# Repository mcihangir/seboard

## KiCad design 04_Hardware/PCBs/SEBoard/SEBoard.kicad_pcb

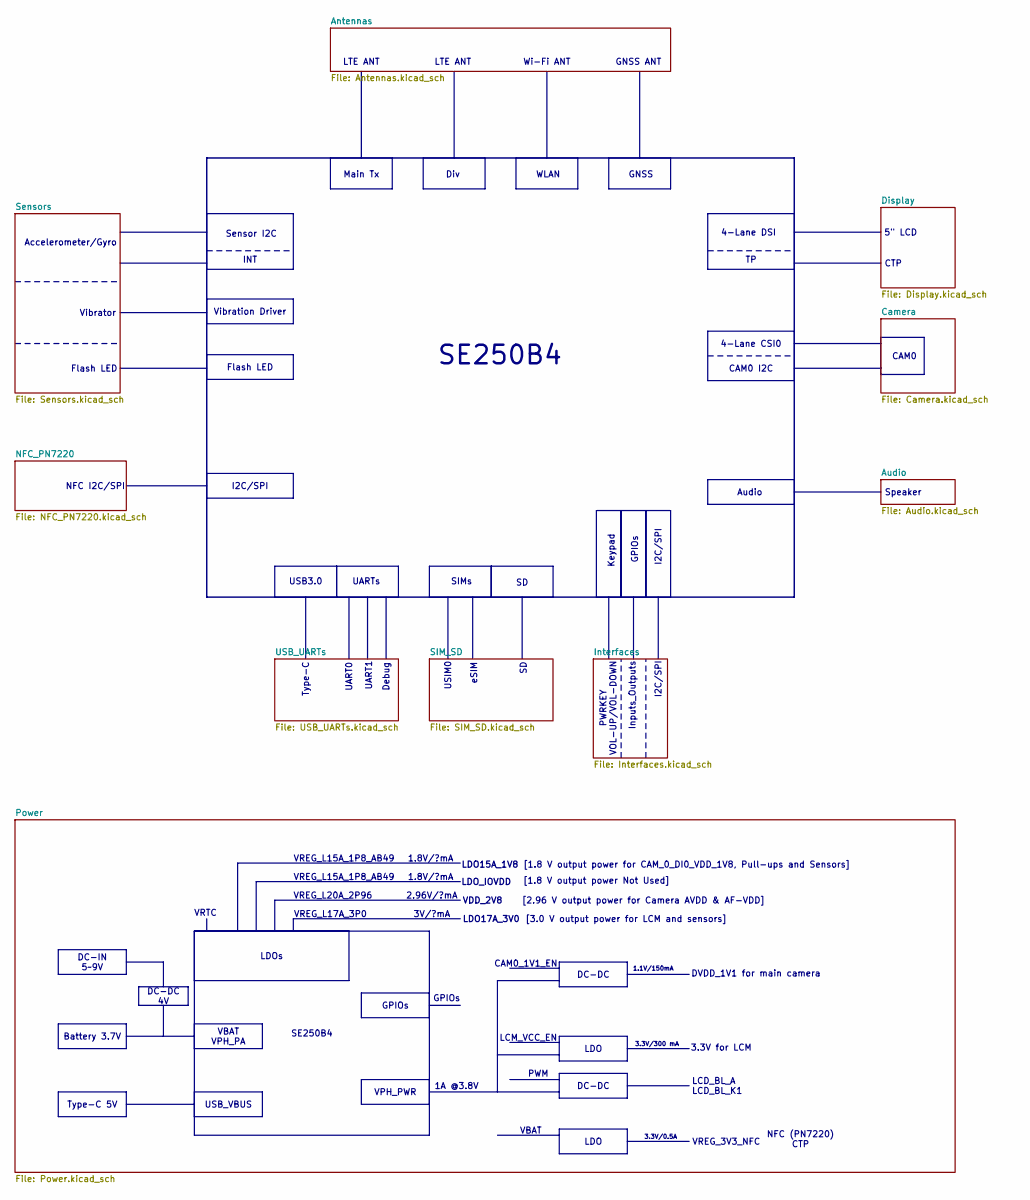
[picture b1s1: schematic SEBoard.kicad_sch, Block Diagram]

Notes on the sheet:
PWRKEY VOL-UP/VOL-DOWN
LDO17A_3V0
VREG_L15A_1P8_AB49
UARTs
Debug
GPIOs
I2C/SPI
Inputs_Outputs
USIM0
[1.8 V output power Not Used]
[3.0 V output power for LCM and sensors]
Flash LED
1.8V/?mA
4-Lane DSI
VRTC
1.1V/150mA
UART0
Accelerometer/Gyro
VREG_L20A_2P96
LCM_VCC_EN
USB3.0
SE250B4
VREG_L17A_3P0
1A @3.8V
Type-C
eSIM
2.96V/?mA
Vibration Driver
4-Lane CSI0
NFC I2C/SPI
Main Tx
Speaker
DVDD_1V1 for main camera
PWM
5" LCD
LCD_BL_A LCD_BL_K1
CAM0
GNSS
VDD_2V8
CAM0 I2C

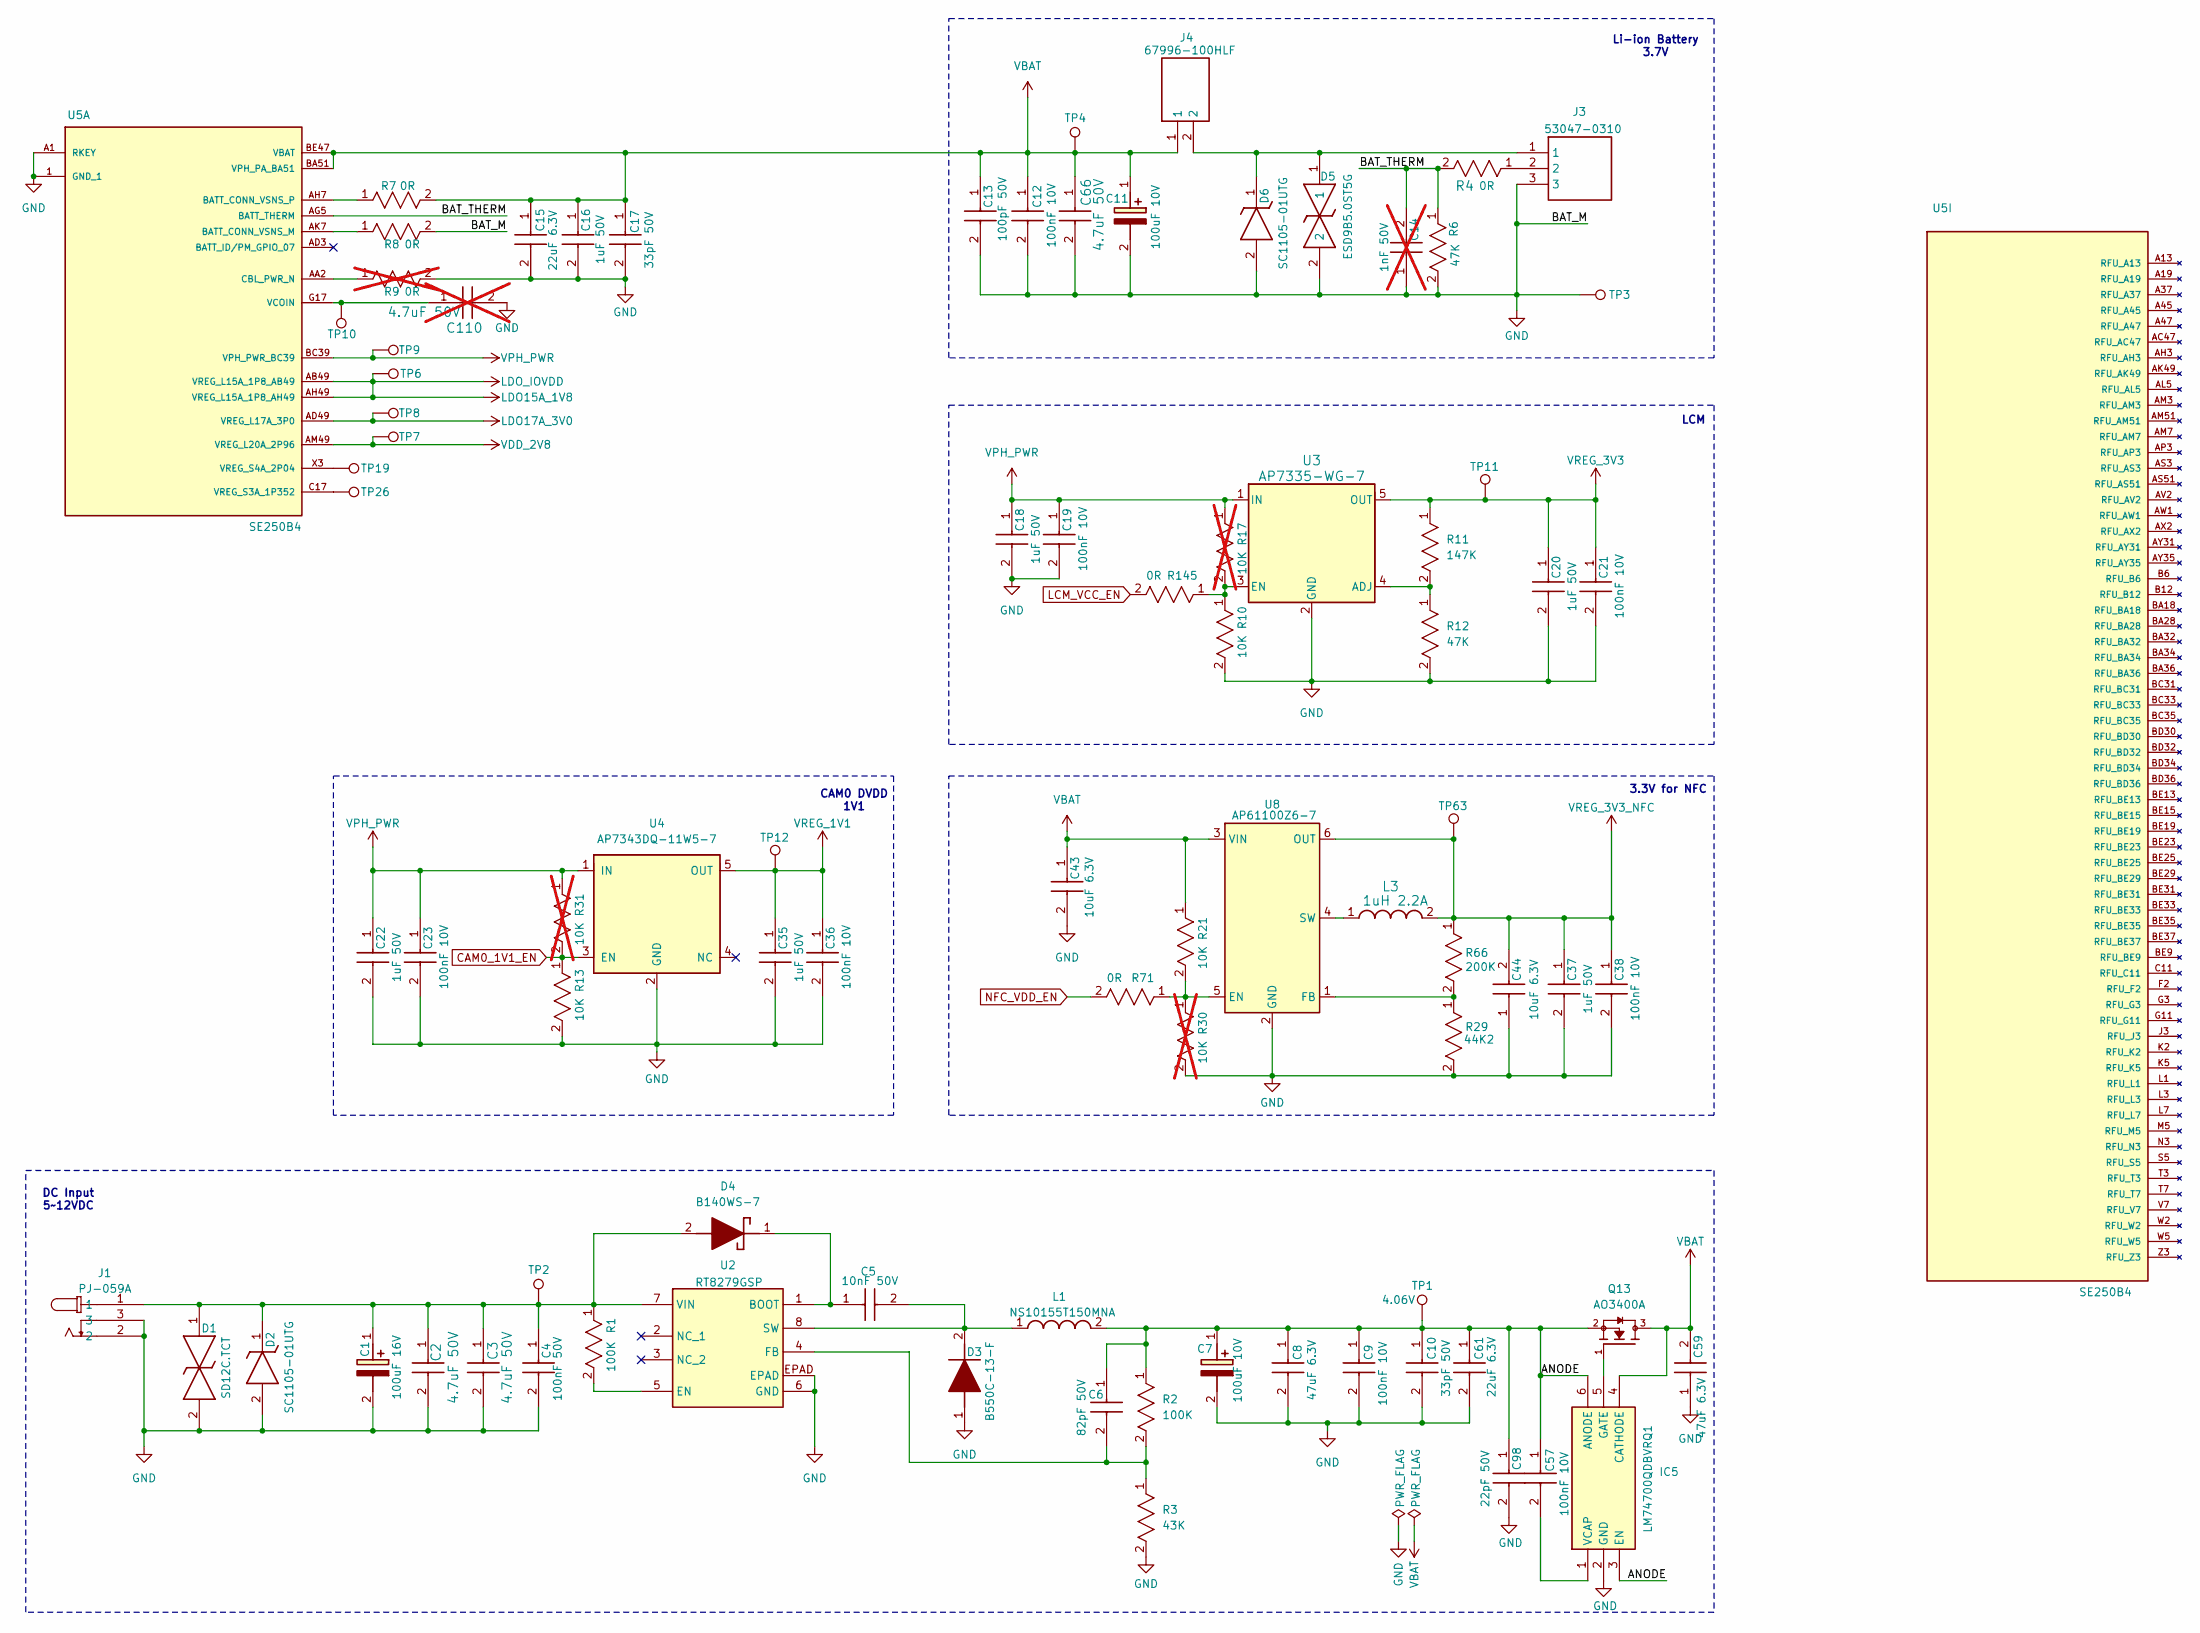
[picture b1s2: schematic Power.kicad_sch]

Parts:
C1: 100uF 16V; T495X; Part Number T495X107M016ATE1007280
C2, C3, C66: 4.7uF 50V; CAP_UMK325B7475MM-T_TAY; Part Number UMK325BJ475MM-T
C4: 100nF 50V; CAPC1005X55N; Part Number UMK105B7104KVHF
C5: 10nF 50V; CAPC1005X55N; Part Number GRM155R71H103KA88D
C6: 82pF 50V; CAPC1005X55N; Part Number GRM1555C1H820JA01D
C7, C11: 100uF 10V; T495D; Part Number T495D107K010ATE080
C8, C59: 47uF 6.3V; GRM31x; Part Number GRM31CR60J476ME19L
C9, C12, C19, C21, C23, C36, C38, C57: 100nF 10V; CAPC1005X55N; Part Number GRM155R71A104KA01D
C10, C17: 33pF 50V; CAPC1005X55N; Part Number GRM1555C1H330JA01D
C13: 100pF 50V; CAPC1005X55N; Part Number GRM1555C1H101JA01J
C14: 1nF 50V; CAPC1005X55N; Part Number GRM1555C1H102JA01D; not fitted
C15, C61: 22uF 6.3V; CAPC1005X55N; Part Number GRM158R60J226ME01D
C16, C18, C20, C22, C35, C37: 1uF 50V; CAPC1005X55N; Part Number GRM155R61H105KE05D
C43, C44: 10uF 6.3V; CAPC1005X55N; Part Number GRM155R60J106ME15D
C98: 22pF 50V; CAPC1005X55N; Part Number GRM1555C1H220JA01D
C110: 4.7uF 50V; CAP_UMK325B7475MM-T_TAY; Part Number UMK325BJ475MM-T; not fitted
D1: SD12C.TCT; SD12CTCT; Part Number SD12C.TCT
D2, D6: SC1105-01UTG; SC110501UTG; Part Number SC1105-01UTG
D3: B550C-13-F; DIOM7959X250N; Part Number B550C-13-F
D4: B140WS-7; SOD2513X120N; Part Number B140WS-7
D5: ESD9B5.0ST5G; SODFL1006X40N; Part Number ESD9B5.0ST5G
IC5: LM74700QDBVRQ1; SOT95P280X145-6N; Part Number LM74700QDBVRQ1
J1: PJ-059A; PJ059A; Part Number PJ-059A
J3: 53047-0310; 530470310; Part Number 53047-0310
J4: 67996-100HLF; HDRV2W67P254_2X1_254X483X858P; Part Number 67996-100HLF
L1: NS10155T150MNA; NS10165T220MNA; Part Number NS10155T150MNA
L3: 1uH 2.2A; IND_WE-LQS_2512_WRE; Part Number 74404024010
Q13: AO3400A; SOT95P280X125-3N; Part Number AO3400A
R1, R2: 100K; RC0402N_YAG; Part Number RC0402JR-07100KL
R3: 43K; RC0402N_YAG; Part Number RC0402JR-0743KL
R4, R7, R8, R71, R145: 0R; RC0402N_YAG; Part Number RC0402JR-070RL
R6, R12: 47K; RC0402N_YAG; Part Number RC0402JR-0747KL
R9: 0R; RC0402N_YAG; Part Number RC0402JR-070RL; not fitted
R10, R13, R21: 10K; RC0402N_YAG; Part Number RC0402JR-0710KL
R11: 147K; RC0402N_YAG; Part Number RC0402FR-07147KL
R17, R30, R31: 10K; RC0402N_YAG; Part Number RC0402JR-0710KL; not fitted
R29: 44K2; RC0402N_YAG; Part Number RC0402FR-0744K2L
R66: 200K; RC0402N_YAG; Part Number RC0402FR-07200KL
TP1, TP2: 4.06V; TestPoint_Pad_D1.0mm
TP3, TP11, TP12, TP63: Sens_P; TestPoint_Pad_D1.0mm
TP4: VBAT; TestPoint_Pad_D1.0mm
TP6, TP19, TP26: LDO_IOVDD; TestPoint_Pad_D1.0mm
TP7: VDD_2V8; TestPoint_Pad_D1.0mm
TP8: LDO17A_3V0; TestPoint_Pad_D1.0mm
TP9: VPH_PWR; TestPoint_Pad_D1.0mm
TP10: VRTC; TestPoint_Pad_D1.0mm
U2: RT8279GSP; SOP8L_EP1_RIT; Part Number RT8279GSP
U3: AP7335-WG-7; SOT95P285X145-5N; Part Number AP7335-WG-7
U4: AP7343DQ-11W5-7; SOT95P285X145-5N; Part Number AP7343DQ-11W5-7
U5: SE250B4; XCVR_SE250B4-NA; Part Number SE250B4-EU
U8: AP61100Z6-7; SOT50P162X60-6N; Part Number AP61100Z6-7

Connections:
/Power/ANODE: C6.1, C7.1 (+), C8.1, C9.1, C10.1, C57.1, C61.1, C98.1, IC5.3 (EN), IC5.6 (ANODE), L1.2, Q13.2, R2.1, TP1.1 (1_1)
/Power/BAT_THERM: C14.2, R4.2, R6.1, U5.AG5 (BATT_THERM)
CAM0_1V1_EN: R13.1, R31.2, U4.3 (EN); also elsewhere on the board
GND: C1.2 (-), C2.2, C3.2, C4.2, C7.2 (-), C8.2, C9.2, C10.2, C11.2 (-), C12.2, C13.2, C14.1, C15.2, C16.2, C17.2, C18.2, C19.2, C20.2, C21.2, C22.2, C23.2, C35.2, C36.2, C37.2, C38.2, C43.2, C44.1, C59.1, C61.2, C66.2, C98.2, C110.2, D1.2, D2.2 (A), D3.1 (A), D5.2, D6.2 (A), IC5.2 (GND), J1.2, J1.3, J3.3, R3.2, R6.2, R8.2, R9.2, R10.2, R12.2, R13.2, R29.2, R30.2, TP3.1 (1_1), U2.6 (GND), U2.EPAD, U3.2 (GND), U4.2 (GND), U5.1 (GND_1), U5.2 (GND_2), U5.3 (GND_3), U5.4 (GND_4), U5.5 (GND_5), U5.6 (GND_6), U5.7 (GND_7), U5.8 (GND_8), U5.9 (GND_9), U5.10 (GND_10), U5.11 (GND_11), U5.12 (GND_12), U5.13 (GND_13), U5.14 (GND_14), U5.15 (GND_15), U5.16 (GND_16), U5.17 (GND_17), U5.18 (GND_18), U5.19 (GND_19), U5.20 (GND_20), U5.21 (GND_21), U5.22 (GND_22), U5.23 (GND_23), U5.24 (GND_24), U5.25 (GND_25), U5.26 (GND_26), U5.27 (GND_27), U5.28 (GND_28), U5.29 (GND_29), U5.30 (GND_30), U5.31 (GND_31), U5.32 (GND_32), U5.33 (GND_33), U5.34 (GND_34), U5.35 (GND_35), U5.36 (GND_36), U5.37 (GND_37), U5.38 (GND_38), U5.39 (GND_39), U5.40 (GND_40), U5.41 (GND_41), U5.42 (GND_42), U5.43 (GND_43), U5.44 (GND_44), U5.45 (GND_45), U5.46 (GND_46), U5.47 (GND_47), U5.48 (GND_48), U5.49 (GND_49), U5.50 (GND_50), U5.51 (GND_51), U5.52 (GND_52), U5.53 (GND_53), U5.54 (GND_54), U5.55 (GND_55), U5.56 (GND_56), U5.57 (GND_57), U5.58 (GND_58), U5.59 (GND_59), U5.60 (GND_60), U5.A1 (RKEY), U5.A7 (GND_A7), U5.A11 (GND_A11), U5.A15 (GND_A15), U5.A17 (GND_A17), U5.A21 (GND_A21), U5.A23 (GND_A23), U5.A27 (GND_A27), U5.A29 (GND_A29), U5.A31 (GND_A31), U5.A35 (GND_A35), U5.A39 (GND_A39), U5.A43 (GND_A43), U5.AA5 (GND_AA5), U5.AA47 (GND_AA47), U5.AB45 (GND_AB45), U5.AB51 (GND_AB51), U5.AC50 (GND_AC50), U5.AD7 (GND_AD7), U5.AE5 (GND_AE5), U5.AF3 (GND_AF3), U5.AF45 (GND_AF45), U5.AG2 (GND_AG2), U5.AH1 (GND_AH1), U5.AH51 (GND_AH51), U5.AJ2 (GND_AJ2), U5.AJ5 (GND_AJ5), U5.AJ47 (GND_AJ47), U5.AK3 (GND_AK3), U5.AK45 (GND_AK45), U5.AK51 (GND_AK51), U5.AL2 (GND_AL2), U5.AL47 (GND_AL47), U5.AM1 (GND_AM1), U5.AM45 (GND_AM45), U5.AN2 (GND_AN2), U5.AN50 (GND_AN50), U5.AP1 (GND_AP1), U5.AP51 (GND_AP51), U5.AR2 (GND_AR2), U5.AS1 (GND_AS1), U5.AT2 (GND_AT2), U5.AU1 (GND_AU1), U5.AU45 (GND_AU45), U5.AU51 (GND_AU51), U5.AV47 (GND_AV47), U5.AV50 (GND_AV50), U5.AW49 (GND_AW49), U5.AY1 (GND_AY1), U5.AY11 (GND_AY11), U5.AY17 (GND_AY17), U5.AY19 (GND_AY19), U5.AY29 (GND_AY29), U5.AY33 (GND_AY33), U5.AY37 (GND_AY37), U5.AY39 (GND_AY39), U5.AY41 (GND_AY41), U5.AZ2 (GND_AZ2), U5.B8 (GND_B8), U5.B10 (GND_B10), U5.B14 (GND_B14), U5.B16 (GND_B16), U5.B18 (GND_B18), U5.B24 (GND_B24), U5.B26 (GND_B26), U5.B28 (GND_B28), U5.B32 (GND_B32), U5.B34 (GND_B34), U5.B40 (GND_B40), U5.B42 (GND_B42), U5.BA1 (GND_BA1), U5.BA12 (GND_BA12), U5.BA20 (GND_BA20), U5.BA26 (GND_BA26), U5.BA30 (GND_BA30), U5.BA38 (GND_BA38), U5.BA40 (GND_BA40), U5.BA42 (GND_BA42), U5.BC13 (GND_BC13), U5.BC23 (GND_BC23), U5.BC29 (GND_BC29), U5.BC37 (GND_BC37), U5.BC45 (GND_BC45), U5.BD14 (GND_BD14), U5.BD24 (GND_BD24), U5.BD38 (GND_BD38), U5.BD44 (GND_BD44), U5.BE7 (GND_BE7), U5.BE11 (GND_BE11), U5.BE17 (GND_BE17), U5.BE21 (GND_BE21), U5.BE27 (GND_BE27), U5.BE39 (GND_BE39), U5.BE41 (GND_BE41), U5.C7 (GND_C7), U5.C9 (GND_C9), U5.C13 (GND_C13), U5.C15 (GND_C15), U5.C33 (GND_C33), U5.C41 (GND_C41), U5.E10 (GND_E10), U5.F50 (GND_F50), U5.G1 (GND_G1), U5.H2 (GND_H2), U5.J1 (GND_J1), U5.J51 (GND_J51), U5.M47 (GND_M47), U5.M50 (GND_M50), U5.N7 (GND_N7), U5.N49 (GND_N49), U5.N51 (GND_N51), U5.P47 (GND_P47), U5.P50 (GND_P50), U5.R3 (GND_R3), U5.T45 (GND_T45), U5.U5 (GND_U5), U5.V3 (GND_V3), U5.X1 (GND_X1), U5.Y2 (GND_Y2), U5.Y5 (GND_Y5), U8.2 (GND); also elsewhere on the board
LCM_VCC_EN: R145.2; also elsewhere on the board
LDO15A_1V8: TP6.1 (1_1), U5.AB49 (VREG_L15A_1P8_AB49), U5.AH49 (VREG_L15A_1P8_AH49); also elsewhere on the board
LDO17A_3V0: TP8.1 (1_1), U5.AD49 (VREG_L17A_3P0); also elsewhere on the board
NFC_VDD_EN: R71.2; also elsewhere on the board
unnamed: C1.1 (+), C2.1, C3.1, C4.1, D1.1, D2.1 (K), D4.2 (A), J1.1, R1.1, TP2.1 (1_1), U2.7 (VIN)
unnamed: C5.2, D3.2 (K), L1.1, U2.8 (SW)
unnamed: C5.1, D4.1 (K), U2.1 (BOOT)
unnamed: D5.1, D6.1 (K), J3.1, J4.2
unnamed: IC5.5 (GATE), Q13.1
unnamed: C57.2, IC5.1 (VCAP)
unnamed: J3.2, R4.1
unnamed: R1.2, U2.5 (EN)
unnamed: C6.2, R2.2, R3.1, U2.4 (FB)
unnamed: R11.2, R12.1, U3.4 (ADJ)
unnamed: R10.1, R17.2, R145.1, U3.3 (EN)
unnamed: R8.1, U5.AK7 (BATT_CONN_VSNS_M)
unnamed: R7.1, U5.AH7 (BATT_CONN_VSNS_P)
unnamed: R9.1, U5.AA2 (CBL_PWR_N)
unnamed: C110.1, TP10.1 (1_1), U5.G17 (VCOIN)
unnamed: TP26.1 (1_1), U5.C17 (VREG_S3A_1P352)
unnamed: TP19.1 (1_1), U5.X3 (VREG_S4A_2P04)
unnamed: R21.2, R30.1, R71.1, U8.5 (EN)
unnamed: R29.1, R66.2, U8.1 (FB)
unnamed: L3.1, U8.4 (SW)
VBAT: C11.1 (+), C12.1, C13.1, C15.1, C16.1, C17.1, C43.1, C59.2, C66.1, IC5.4 (CATHODE), J4.1, Q13.3, R7.2, R21.1, TP4.1 (1_1), U5.AW51 (VPH_PA_AW51), U5.AX50 (VPH_PA_AX50), U5.AY49 (VPH_PA_AY49), U5.AY51 (VPH_PA_AY51), U5.AZ50 (VPH_PA_AZ50), U5.BA51 (VPH_PA_BA51), U5.BC41 (VPH_PA_BC41), U5.BD42 (VPH_PA_BD42), U5.BE47 (VBAT), U8.3 (VIN); also elsewhere on the board
VDD_2V8: TP7.1 (1_1), U5.AM49 (VREG_L20A_2P96); also elsewhere on the board
VPH_PWR: C18.1, C19.1, C22.1, C23.1, R17.1, R31.1, TP9.1 (1_1), U3.1 (IN), U4.1 (IN), U5.BC39 (VPH_PWR_BC39), U5.BC43 (VPH_PWR_BC43), U5.BD40 (VPH_PWR_BD40), U5.BD46 (VPH_PWR_BD46), U5.BE43 (VPH_PWR_BE43), U5.BE45 (VPH_PWR_BE45); also elsewhere on the board
VREG_1V1: C35.1, C36.1, TP12.1 (1_1), U4.5 (OUT); also elsewhere on the board
VREG_3V3: C20.1, C21.1, R11.1, TP11.1 (1_1), U3.5 (OUT); also elsewhere on the board
VREG_3V3_NFC: C37.1, C38.1, C44.2, L3.2, R66.1, TP63.1 (1_1), U8.6 (OUT); also elsewhere on the board

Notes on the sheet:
3.3V for NFC
Li-ion Battery 3.7V
CAM0 DVDD 1V1
LCM
DC Input 5~12VDC

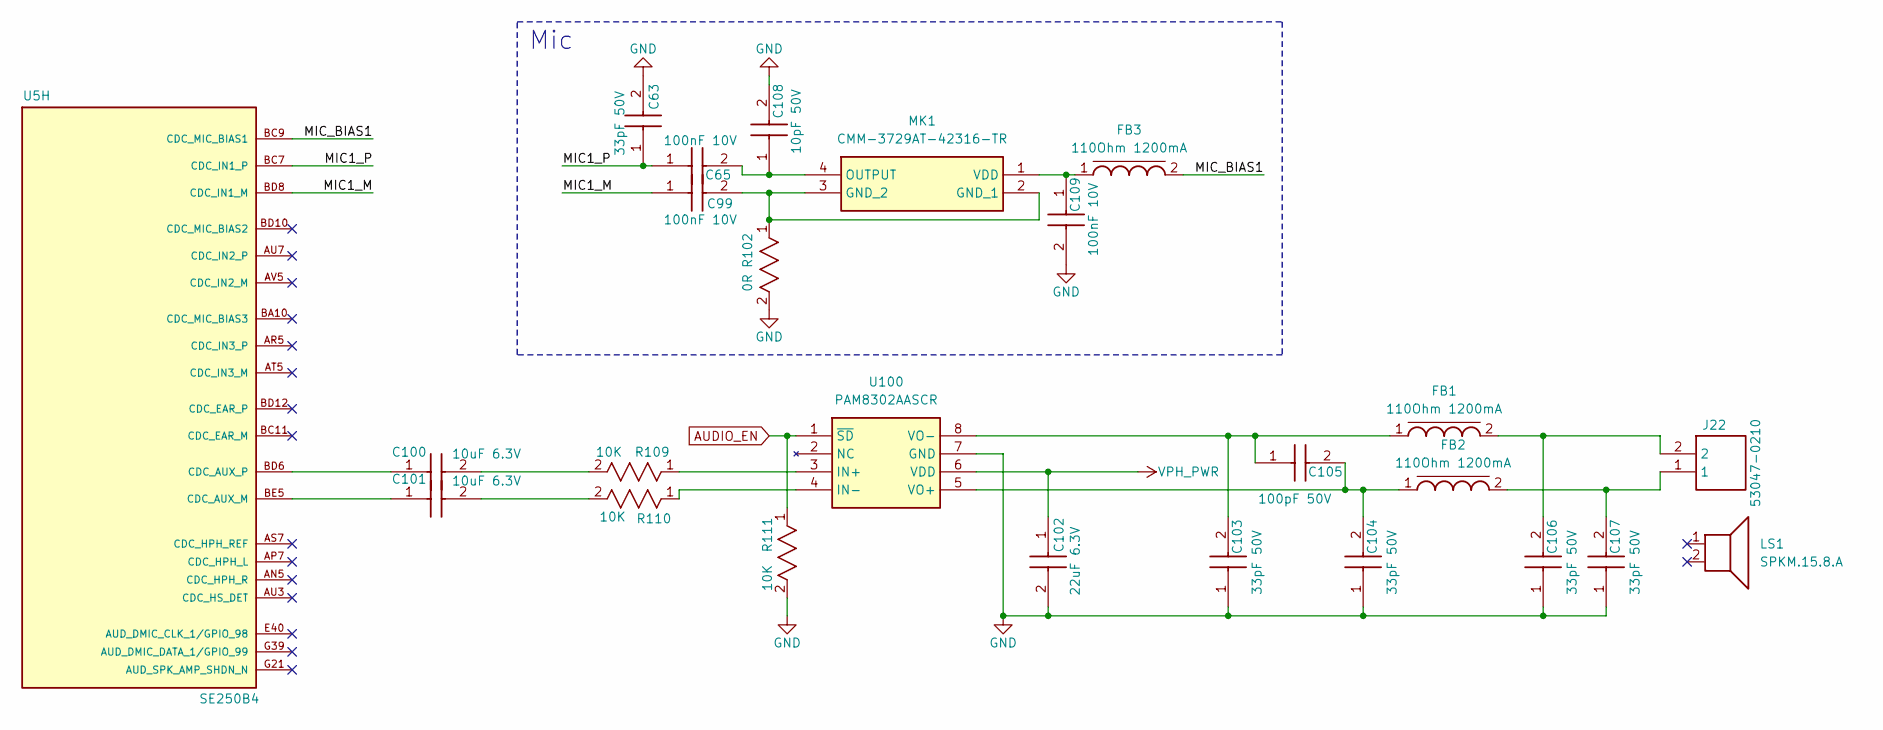
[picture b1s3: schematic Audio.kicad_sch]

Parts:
C63, C103, C104, C106, C107: 33pF 50V; CAPC1005X55N; Part Number GRM1555C1H330JA01D
C65, C99, C109: 100nF 10V; CAPC1005X55N; Part Number GRM155R71A104KA01D
C100, C101: 10uF 6.3V; CAPC1005X55N; Part Number GRM155R60J106ME15D
C102: 22uF 6.3V; CAPC1005X55N; Part Number GRM158R60J226ME01D
C105: 100pF 50V; CAPC1005X55N; Part Number GRM1555C1H101JA01J
C108: 10pF 50V; CAPC1005X55N; Part Number GRM1555C1H100JA01D
FB1, FB2, FB3: 110Ohm 1200mA; BEADC1005X55N; Part Number 74269242111
J22: 53047-0210; 530470210; Part Number 53047-0210
LS1: SPKM.15.8.A; Part Number SPKM.15.8.A
MK1: CMM-3729AT-42316-TR; CMM3729AT42316TR; Part Number CMM-3729AT-42316-TR
R102: 0R; RC0402N_YAG; Part Number RC0402JR-070RL
R109, R110, R111: 10K; RC0402N_YAG; Part Number RC0402JR-0710KL
U5: SE250B4; XCVR_SE250B4-NA; Part Number SE250B4-EU
U100: PAM8302AASCR; SOP65P490X110-8N; Part Number PAM8302AASCR

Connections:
/Audio/MIC1_M: C99.1, U5.BD8 (CDC_IN1_M)
/Audio/MIC1_P: C63.1, C65.1, U5.BC7 (CDC_IN1_P)
/Audio/MIC_BIAS1: FB3.2, U5.BC9 (CDC_MIC_BIAS1)
AUDIO_EN: R111.1, U100.1 (~SD); also elsewhere on the board
GND: C63.2, C102.2, C103.1, C104.1, C106.1, C107.1, C108.2, C109.2, R102.2, R111.2, U100.7 (GND); also elsewhere on the board
unnamed: C100.2, R109.2
unnamed: C101.2, R110.2
unnamed: C106.2, FB1.2, J22.2
unnamed: C107.2, FB2.2, J22.1
unnamed: C99.2, MK1.2 (GND_1), MK1.3 (GND_2), R102.1
unnamed: C65.2, C108.1, MK1.4 (OUTPUT)
unnamed: C109.1, FB3.1, MK1.1 (VDD)
unnamed: C101.1, U5.BE5 (CDC_AUX_M)
unnamed: C100.1, U5.BD6 (CDC_AUX_P)
unnamed: R109.1, U100.3 (IN+)
unnamed: R110.1, U100.4 (IN-)
unnamed: C104.2, C105.2, FB2.1, U100.5 (VO+)
unnamed: C103.2, C105.1, FB1.1, U100.8 (VO-)
VPH_PWR: C102.1, U100.6 (VDD); also elsewhere on the board

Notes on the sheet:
Mic

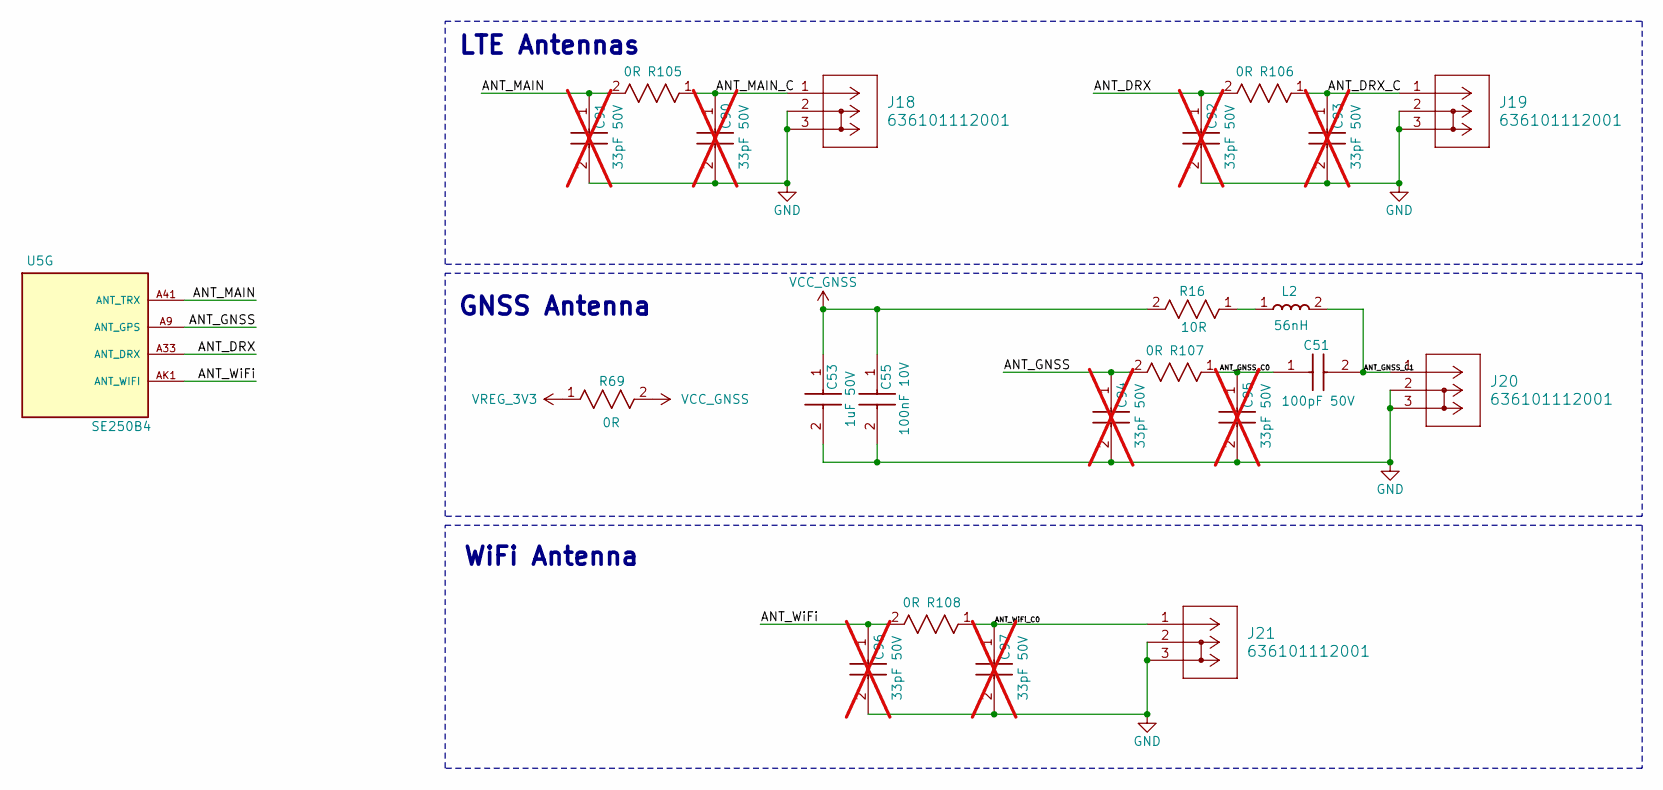
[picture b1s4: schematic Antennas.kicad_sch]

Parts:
C51: 100pF 50V; CAPC1005X55N; Part Number GRM1555C1H101JA01J
C53: 1uF 50V; CAPC1005X55N; Part Number GRM155R61H105KE05D
C55: 100nF 10V; CAPC1005X55N; Part Number GRM155R71A104KA01D
C90, C91, C92, C93, C94, C95, C96, C97: 33pF 50V; CAPC1005X55N; Part Number GRM1555C1H330JA01D; not fitted
J18, J19, J20, J21: 636101112001; COAX2_636101112001_WRE; Part Number 636101112001
L2: 56nH; INDC1005X60N; Part Number 744784156A
R16: 10R; RC0402N_YAG; Part Number RC0402JR-0710RL
R69: 0R; RESC2012X50N; Mouser Part Number 71-CRCW0805-0-E3
R105, R106, R107, R108: 0R; RC0402N_YAG; Part Number RC0402JR-070RL
U5: SE250B4; XCVR_SE250B4-NA; Part Number SE250B4-EU

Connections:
/Antennas/ANT_DRX: C92.1, R106.2, U5.A33 (ANT_DRX)
/Antennas/ANT_DRX_C: C93.1, J19.1 (SIGNAL), R106.1
/Antennas/ANT_GNSS: C94.1, R107.2, U5.A9 (ANT_GPS)
/Antennas/ANT_GNSS_C0: C51.1, C95.1, R107.1
/Antennas/ANT_GNSS_C1: C51.2, J20.1 (SIGNAL), L2.2
/Antennas/ANT_MAIN: C91.1, R105.2, U5.A41 (ANT_TRX)
/Antennas/ANT_MAIN_C: C90.1, J18.1 (SIGNAL), R105.1
/Antennas/ANT_WiFi: C96.1, R108.2, U5.AK1 (ANT_WIFI)
/Antennas/ANT_WiFi_C0: C97.1, J21.1 (SIGNAL), R108.1
GND: C53.2, C55.2, C90.2, C91.2, C92.2, C93.2, C94.2, C95.2, C96.2, C97.2, J18.2 (GND), J18.3 (GND), J19.2 (GND), J19.3 (GND), J20.2 (GND), J20.3 (GND), J21.2 (GND), J21.3 (GND); also elsewhere on the board
unnamed: L2.1, R16.1
VCC_GNSS: C53.1, C55.1, R16.2, R69.2
VREG_3V3: R69.1; also elsewhere on the board

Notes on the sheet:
WiFi Antenna
LTE Antennas
GNSS Antenna

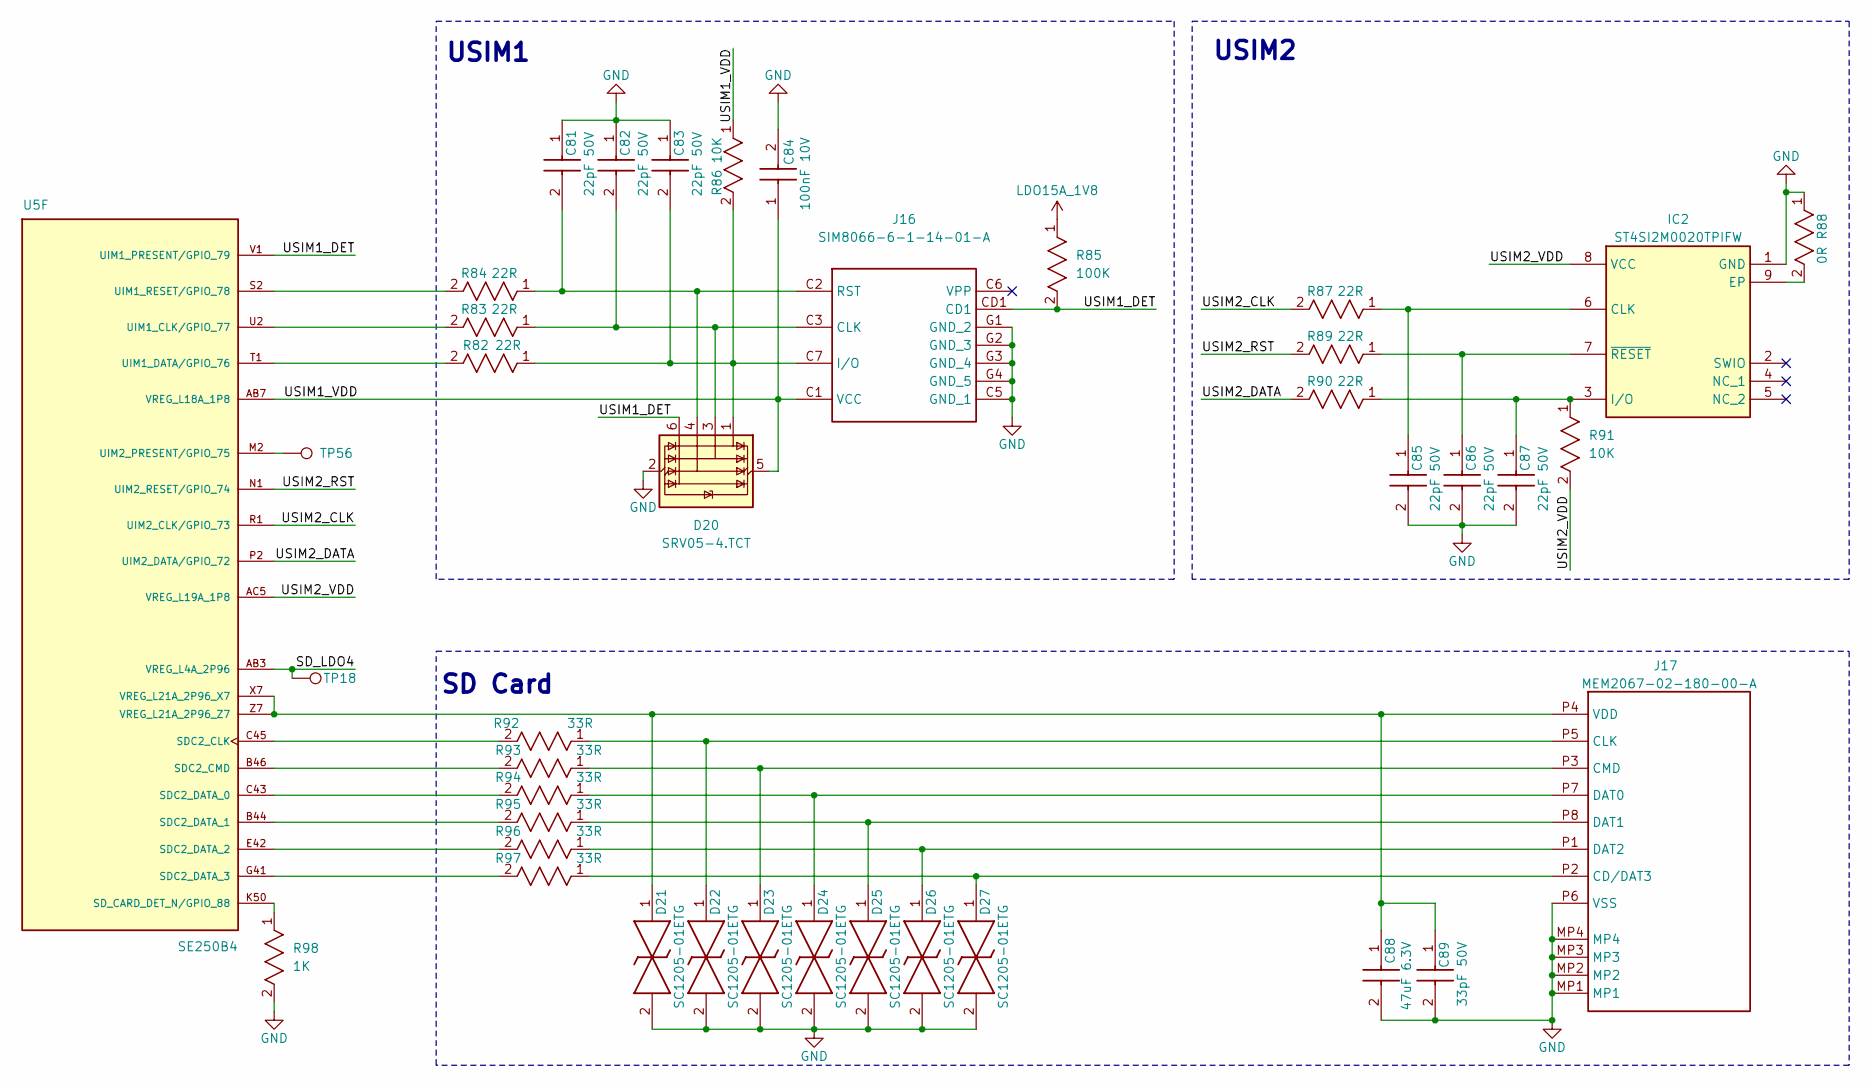
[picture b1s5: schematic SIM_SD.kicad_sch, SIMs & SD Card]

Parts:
C81, C82, C83, C85, C86, C87: 22pF 50V; CAPC1005X55N; Part Number GRM1555C1H220JA01D
C84: 100nF 10V; CAPC1005X55N; Part Number GRM155R71A104KA01D
C88: 47uF 6.3V; GRM31x; Part Number GRM31CR60J476ME19L
C89: 33pF 50V; CAPC1005X55N; Part Number GRM1555C1H330JA01D
D20: SRV05-4.TCT; SOT95P280X145-6N; Part Number SRV05-4.TCT
D21, D22, D23, D24, D25, D26, D27: SC1205-01ETG; SC120501ETG; Part Number SC1205-01ETG
IC2: ST4SI2M0020TPIFW; SON127P600X500X100-9N; Part Number ST4SI2M0020TPIFW
J16: SIM8066-6-1-14-01-A; SIM8066611401A; Part Number SIM8066-6-1-14-01-A
J17: MEM2067-02-180-00-A; MEM20670218000A; Part Number MEM2067-02-180-00-A
R82, R83, R84, R87, R89, R90: 22R; RC0402N_YAG; Part Number RC0402JR-0722RL
R85: 100K; RC0402N_YAG; Part Number RC0402JR-07100KL
R86, R91: 10K; RC0402N_YAG; Part Number RC0402JR-0710KL
R88: 0R; RC0402N_YAG; Part Number RC0402JR-070RL
R92, R93, R94, R95, R96, R97: 33R; RC0402N_YAG; Part Number RC0402JR-0733RL
R98: 1K; RC0402N_YAG; Part Number RC0402JR-071KL
TP18: Sens_M; TestPoint_Pad_D1.0mm
TP56: VBAT; TestPoint_Pad_D1.0mm
U5: SE250B4; XCVR_SE250B4-NA; Part Number SE250B4-EU

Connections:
/SIM_SD/SD_LDO4: TP18.1 (1_1), U5.AB3 (VREG_L4A_2P96)
/SIM_SD/USIM1_DET: D20.6 (I/O4), J16.CD1, R85.2, U5.V1 (UIM1_PRESENT/GPIO_79)
/SIM_SD/USIM1_VDD: C84.1, D20.5 (VBUS), J16.C1 (VCC), R86.1, U5.AB7 (VREG_L18A_1P8)
/SIM_SD/USIM2_CLK: R87.2, U5.R1 (UIM2_CLK/GPIO_73)
/SIM_SD/USIM2_DATA: R90.2, U5.P2 (UIM2_DATA/GPIO_72)
/SIM_SD/USIM2_RST: R89.2, U5.N1 (UIM2_RESET/GPIO_74)
/SIM_SD/USIM2_VDD: IC2.8 (VCC), R91.2, U5.AC5 (VREG_L19A_1P8)
GND: C81.1, C82.1, C83.1, C84.2, C85.2, C86.2, C87.2, C88.2, C89.2, D20.2 (GND), D21.2, D22.2, D23.2, D24.2, D25.2, D26.2, D27.2, IC2.1 (GND), J16.C5 (GND_1), J16.G1 (GND_2), J16.G2 (GND_3), J16.G3 (GND_4), J16.G4 (GND_5), J17.MP1, J17.MP2, J17.MP3, J17.MP4, J17.P6 (VSS), R88.1, R98.2; also elsewhere on the board
LDO15A_1V8: R85.1; also elsewhere on the board
unnamed: C83.2, D20.1 (I/O1), J16.C7 (I/O), R82.1, R86.2
unnamed: C82.2, D20.3 (I/O2), J16.C3 (CLK), R83.1
unnamed: C81.2, D20.4 (I/O3), J16.C2 (RST), R84.1
unnamed: C85.1, IC2.6 (CLK), R87.1
unnamed: IC2.9 (EP), R88.2
unnamed: C87.1, IC2.3 (I/O), R90.1, R91.1
unnamed: C86.1, IC2.7 (~RESET), R89.1
unnamed: D27.1, J17.P2 (CD/DAT3), R97.1
unnamed: D22.1, J17.P5 (CLK), R92.1
unnamed: D23.1, J17.P3 (CMD), R93.1
unnamed: D24.1, J17.P7 (DAT0), R94.1
unnamed: D25.1, J17.P8 (DAT1), R95.1
unnamed: D26.1, J17.P1 (DAT2), R96.1
unnamed: C88.1, C89.1, D21.1, J17.P4 (VDD), U5.X7 (VREG_L21A_2P96_X7), U5.Z7 (VREG_L21A_2P96_Z7)
unnamed: R92.2, U5.C45 (SDC2_CLK)
unnamed: R93.2, U5.B46 (SDC2_CMD)
unnamed: R94.2, U5.C43 (SDC2_DATA_0)
unnamed: R95.2, U5.B44 (SDC2_DATA_1)
unnamed: R96.2, U5.E42 (SDC2_DATA_2)
unnamed: R97.2, U5.G41 (SDC2_DATA_3)
unnamed: R98.1, U5.K50 (SD_CARD_DET_N/GPIO_88)
unnamed: R83.2, U5.U2 (UIM1_CLK/GPIO_77)
unnamed: R82.2, U5.T1 (UIM1_DATA/GPIO_76)
unnamed: R84.2, U5.S2 (UIM1_RESET/GPIO_78)
unnamed: TP56.1 (1_1), U5.M2 (UIM2_PRESENT/GPIO_75)

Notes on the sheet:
USIM2
USIM1
SD Card
